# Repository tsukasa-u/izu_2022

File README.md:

# izu_2022
 
.sch & .brd can be opened with Eagle

2022伊豆大島共同打上実験で打ち上げる要諦だった機体に搭載されていた基板です。打ち上げ用ではありますが、回路に不具合があるため動作は保証できません。

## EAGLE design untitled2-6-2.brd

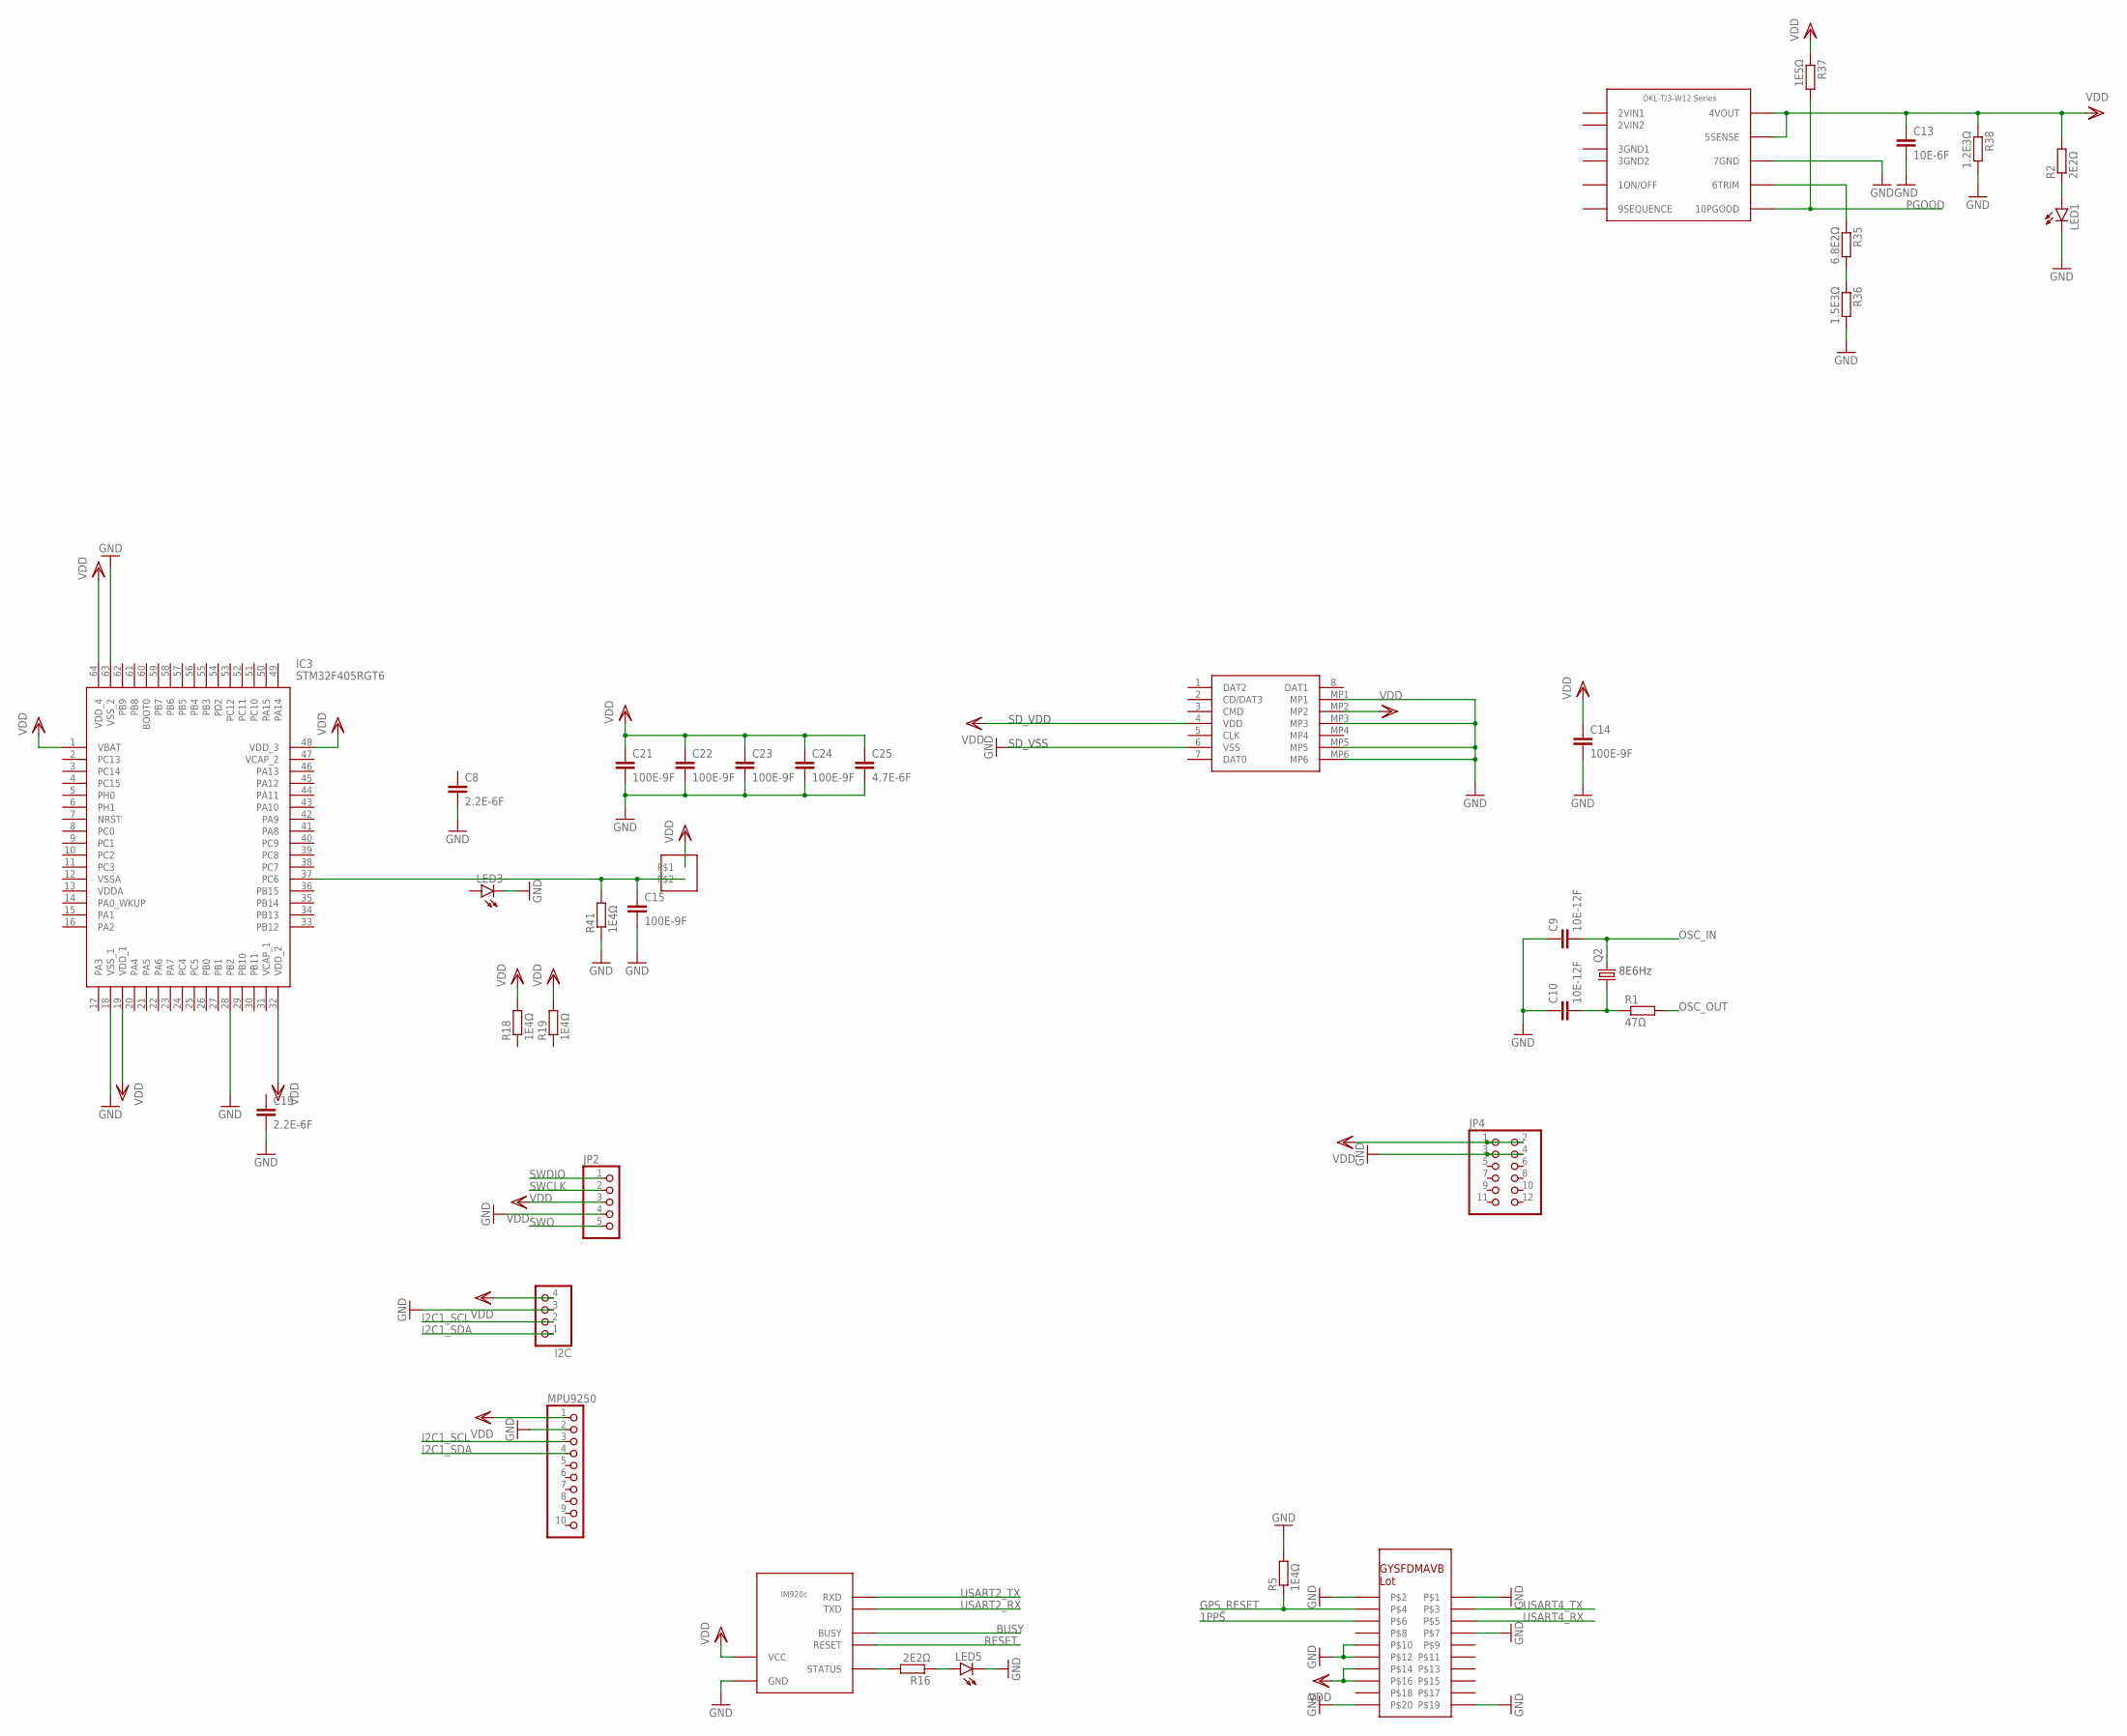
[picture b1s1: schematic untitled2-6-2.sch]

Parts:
C8, C19: 2.2E-6F; C0805
C9, C10: 10E-12F; C0805
C13: 10E-6F; C0805
C14, C15, C21, C22, C23, C24: 100E-9F; C0805
C25: 4.7E-6F; C0805
I2C: PINHD-1X4; 1X04
IC3: STM32F405RGT6; QFP50P1200X1200X160-64N
J1: DM3AT-SF-PEJM5; DM3ATSFPEJM5
JP2: PINHD-1X5; 1X05
JP4: PINHD-2X6; 2X06
LED1, LED3, LED5: LEDCHIP-LED0805; CHIP-LED0805
MPU9250: PINHD-1X10; 1X10
Q2: CRYSTALCTS406; CTS406
R1: 47Ω; R0603
R2, R16: 2E2Ω; R0603
R5, R18, R19, R41: 1E4Ω; R0603
R35: 6.8E2Ω; R0603
R36: 1.5E3Ω; R0603
R37: 1E5Ω; R0603
R38: 1.2E3Ω; R0603
U$3: OKL-T/3-W12SERIES
U$4: GYSFDMAXB_LOT
U$5: IM920C
U$10: B2B-XH-A

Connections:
1PPS: U$4.P$6
BUSY: U$5.BUSY
GND: C8.2, C9.1, C10.1, C13.2, C14.2, C15.2, C19.2, C21.2, C22.2, C23.2, C24.2, C25.2, I2C.3, IC3.18 (VSS_1), IC3.28 (PB2), IC3.63 (VSS_2), J1.6 (VSS), J1.MP1, J1.MP3, J1.MP5, J1.MP6, JP2.4, JP4.3, JP4.4, LED1.C, LED3.C, LED5.C, MPU9250.2, R5.2, R36.2, R38.2, R41.1, U$3.7GND, U$4.P$1, U$4.P$2, U$4.P$7, U$4.P$10, U$4.P$12, U$4.P$19, U$4.P$20, U$5.GND
GPS_RESET: R5.1, U$4.P$4
I2C1_SCL: I2C.2, MPU9250.3
I2C1_SDA: I2C.1, MPU9250.4
unnamed: R16.2, U$5.STATUS
unnamed: LED1.A, R2.1
unnamed: C15.1, IC3.37 (PC6), R41.2, U$10.P$2
unnamed: C10.2, Q2.1, R1.1
unnamed: R35.1, U$3.6TRIM
unnamed: R35.2, R36.1
unnamed: LED5.A, R16.1
OSC_IN: C9.2, Q2.3 (2)
OSC_OUT: R1.2
PGOOD: R37.2, U$3.10PGOOD
RESET: U$5.RESET
SWCLK: JP2.2
SWDIO: JP2.1
SWO: JP2.5
USART2_RX: U$5.TXD
USART2_TX: U$5.RXD
USART4_RX: U$4.P$5
USART4_TX: U$4.P$3
VDD: C13.1, C14.1, C21.1, C22.1, C23.1, C24.1, C25.1, I2C.4, IC3.1 (VBAT), IC3.19 (VDD_1), IC3.32 (VDD_2), IC3.48 (VDD_3), IC3.64 (VDD_4), J1.4 (VDD), J1.MP2, JP2.3, JP4.1, JP4.2, MPU9250.1, R2.2, R18.2, R19.2, R37.1, R38.1, U$3.4VOUT, U$3.5SENSE, U$4.P$14, U$4.P$16, U$5.VCC, U$10.P$1

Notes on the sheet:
8E6Hz
SD_VDD
SD_VSS

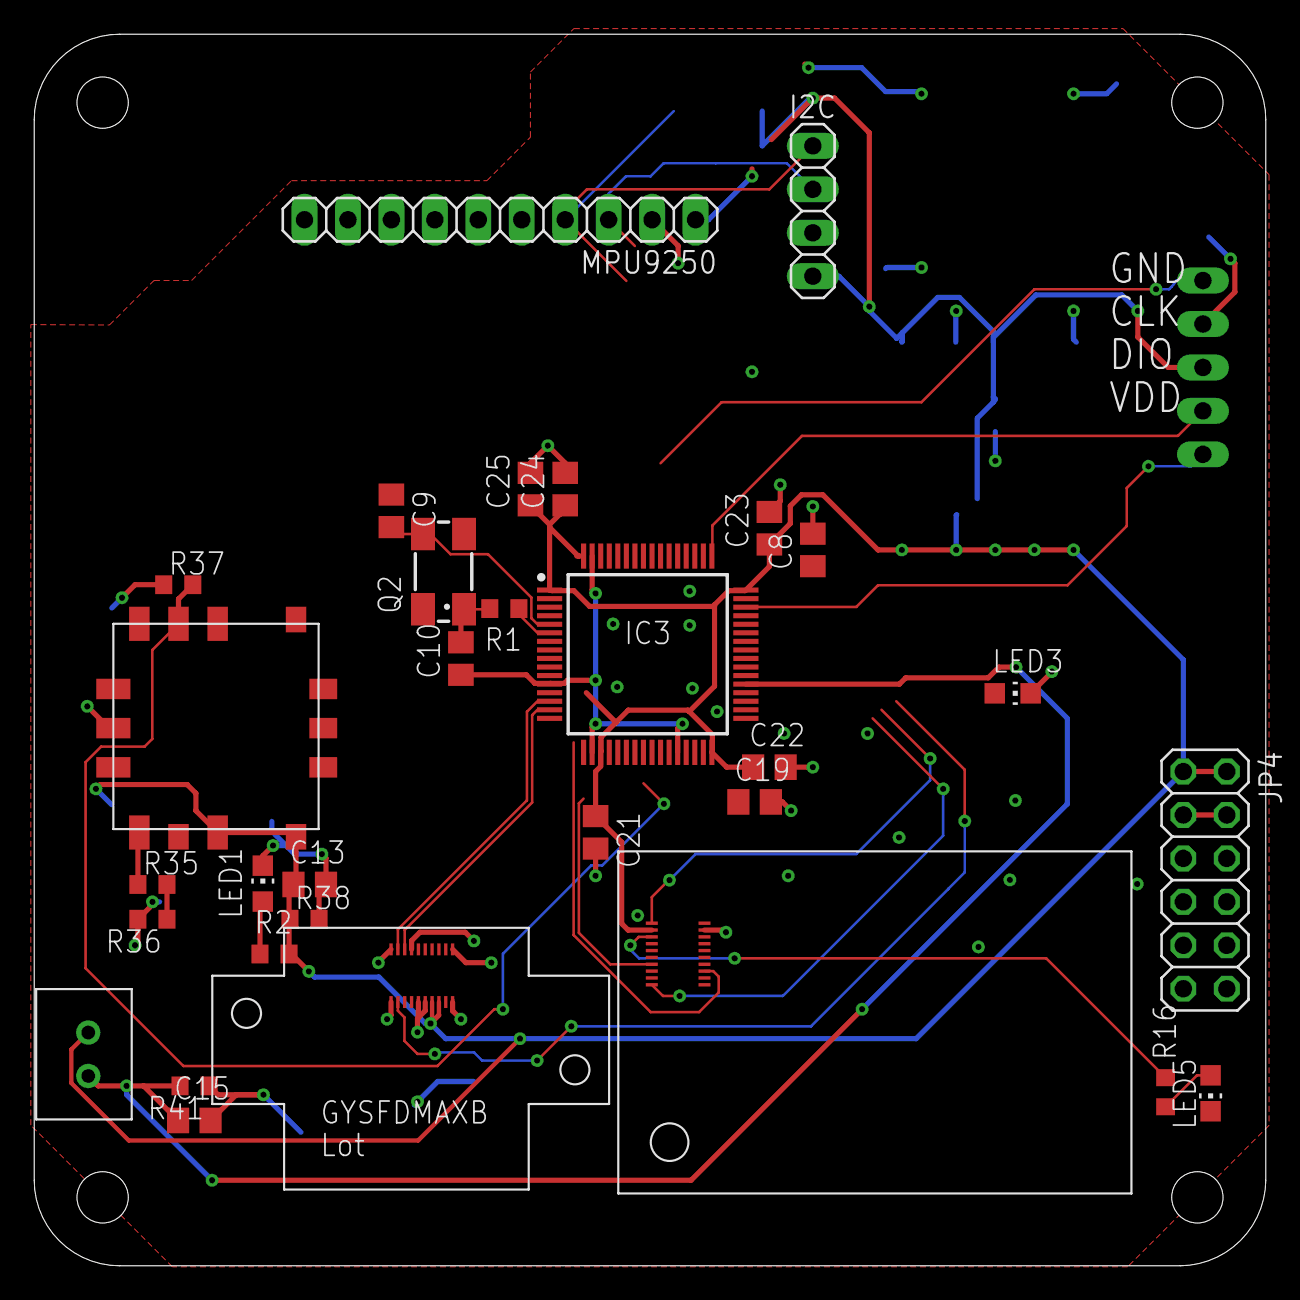
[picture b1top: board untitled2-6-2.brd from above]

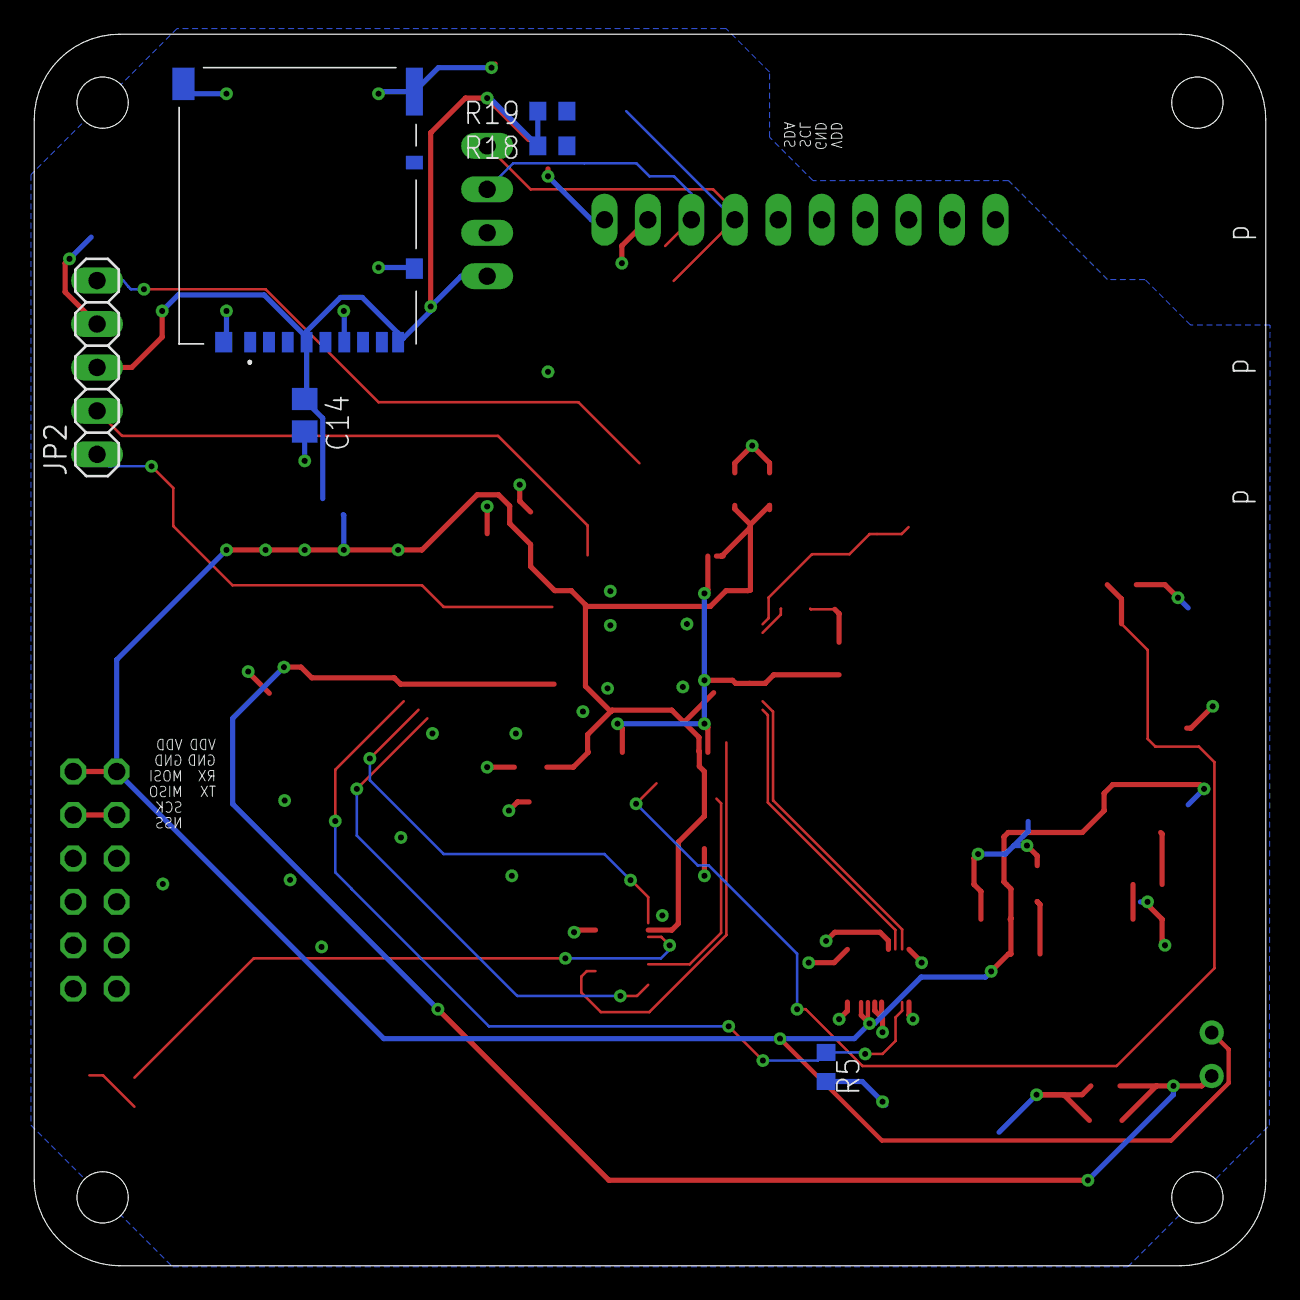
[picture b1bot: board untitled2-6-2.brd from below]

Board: 2 copper layers, 72.0 x 72.0 mm, 37 parts (6 on the bottom side), 14 nets.

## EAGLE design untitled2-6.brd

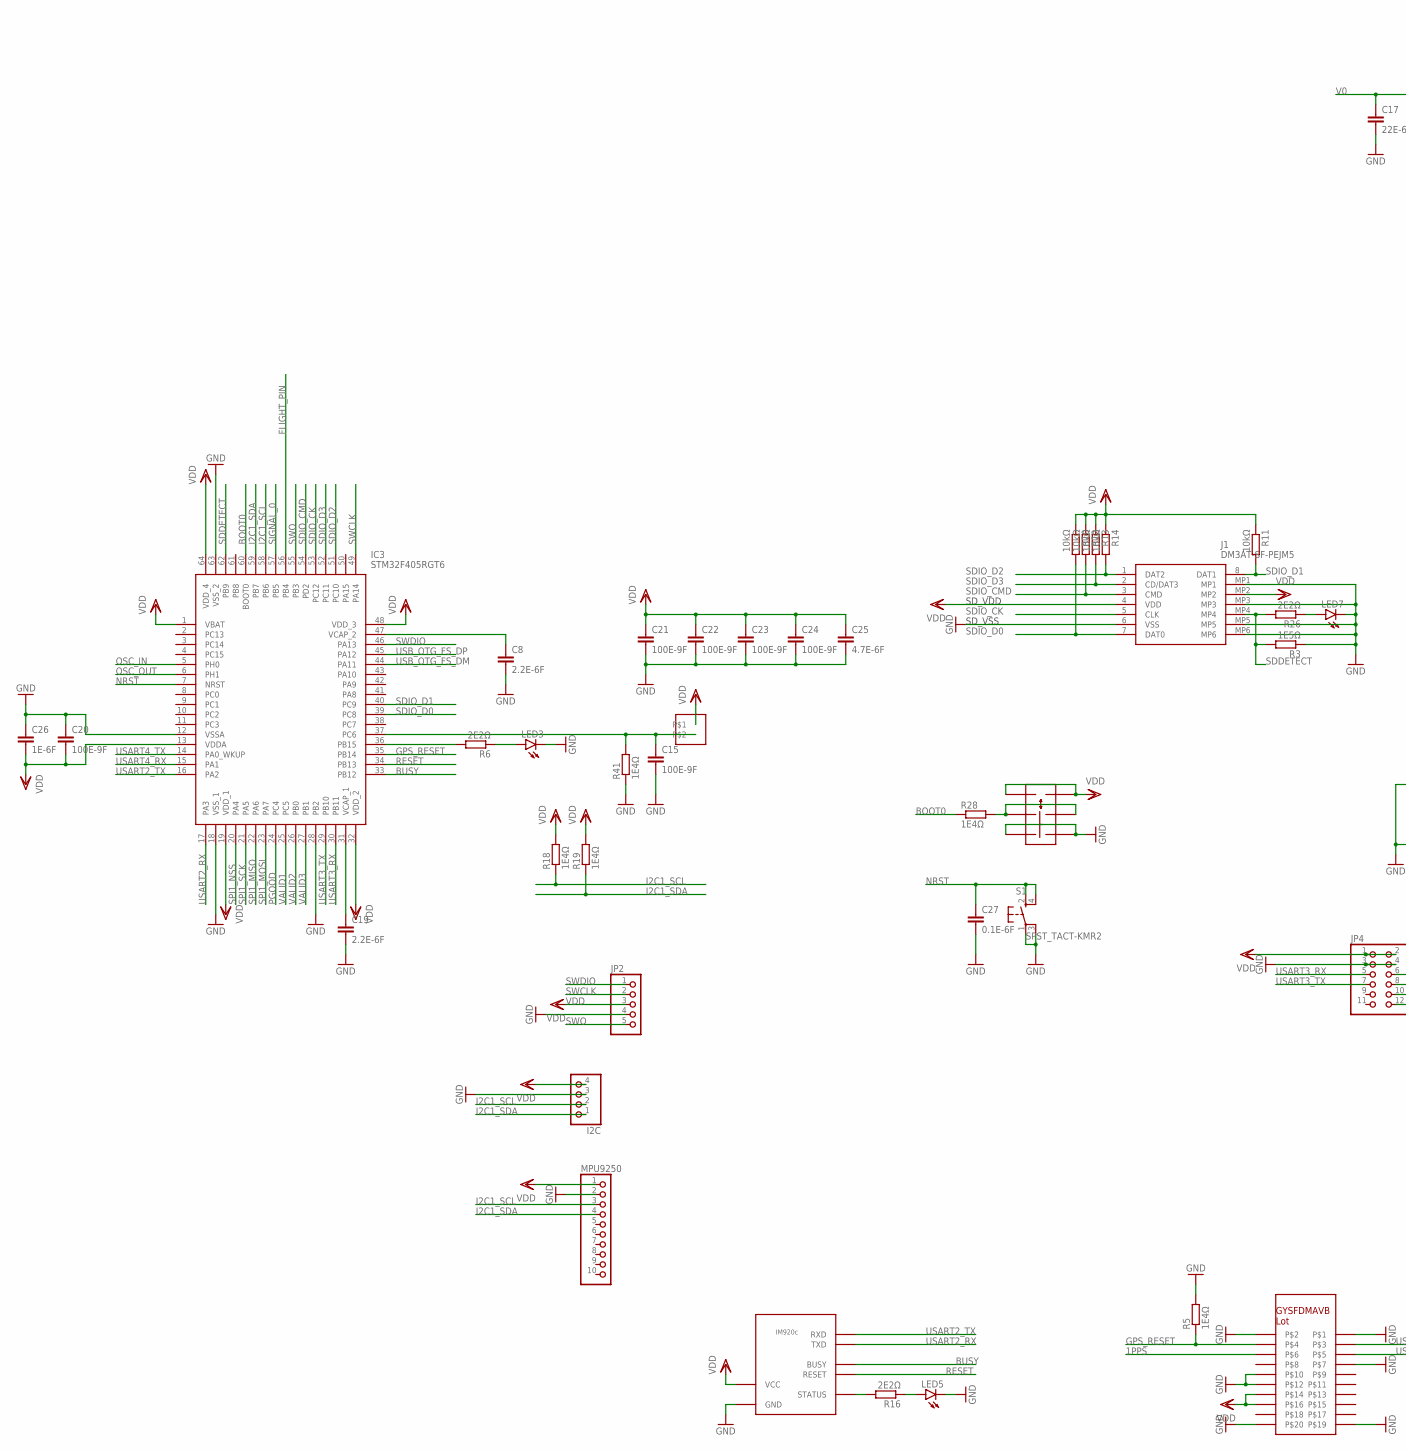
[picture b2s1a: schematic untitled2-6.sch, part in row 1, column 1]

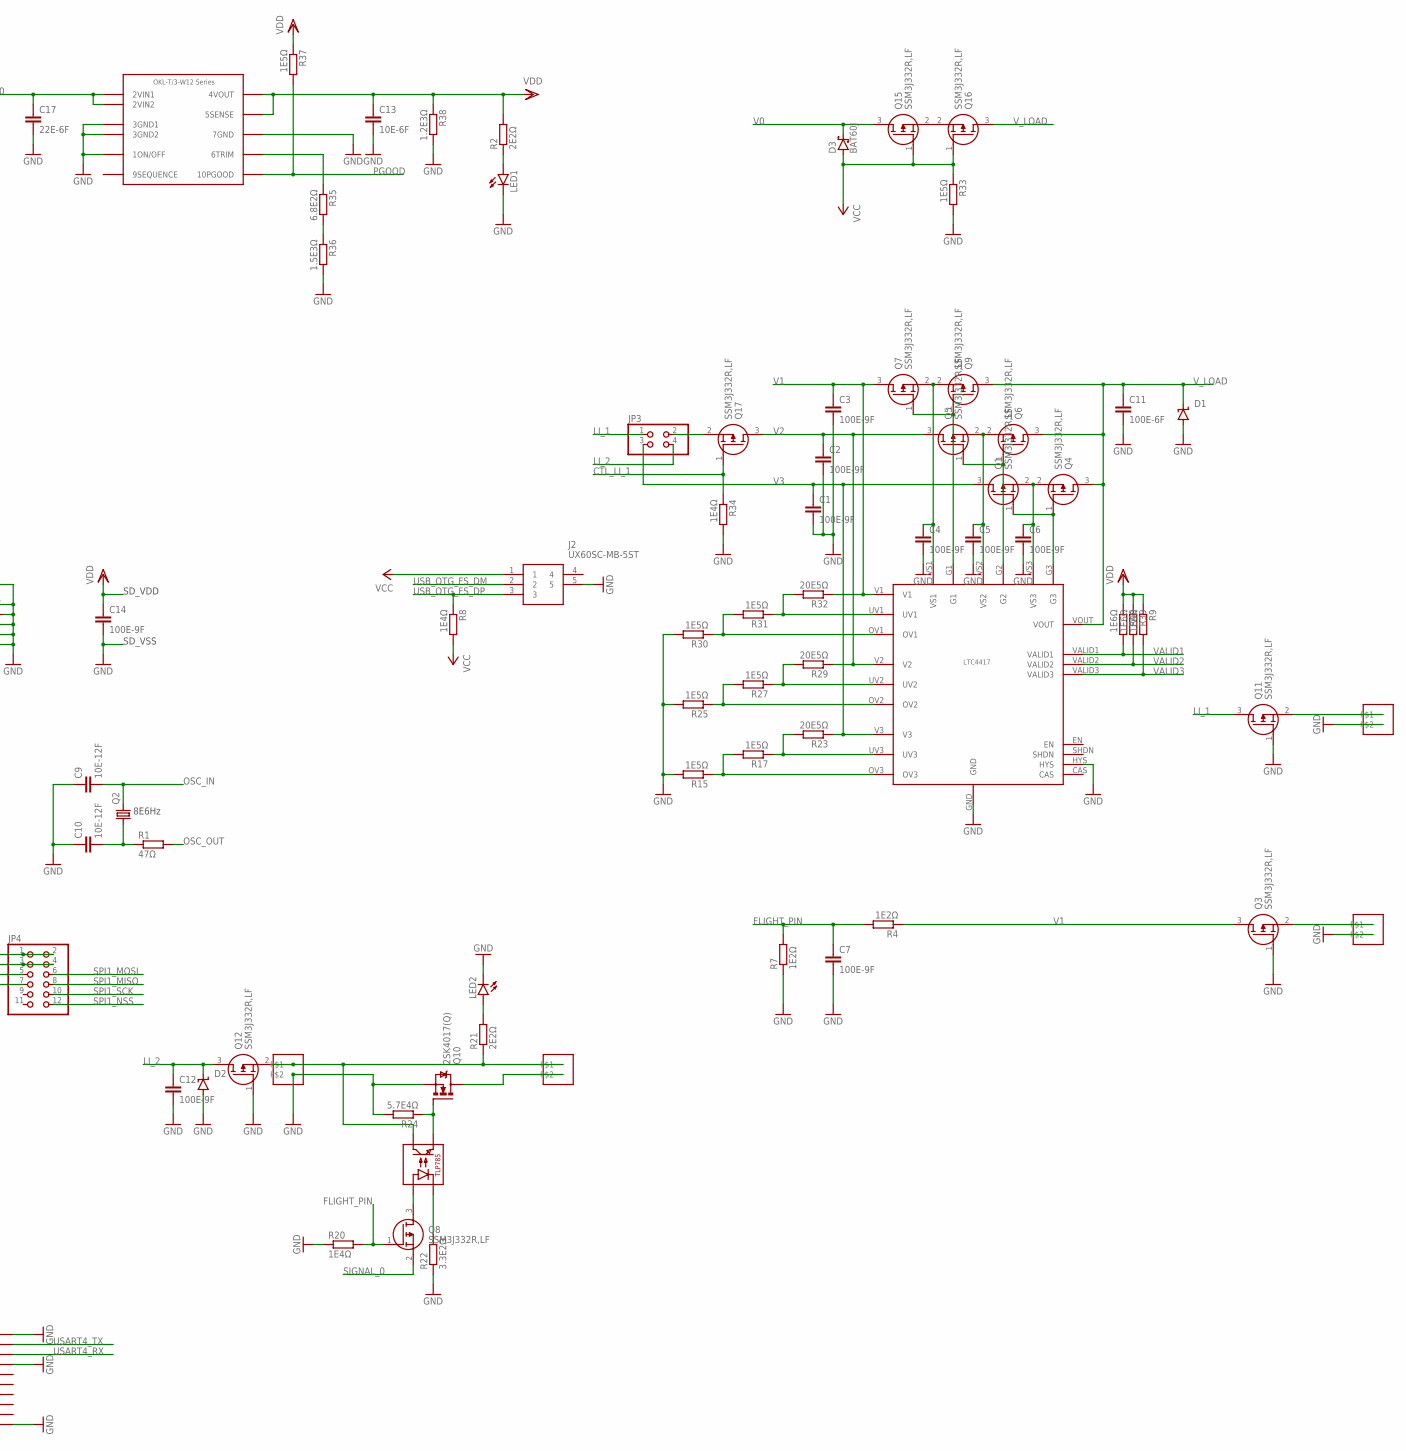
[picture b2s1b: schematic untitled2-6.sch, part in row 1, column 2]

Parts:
C1, C2, C3, C4, C5, C6, C7, C12, C14, C15, C20, C21, C22, C23, C24: 100E-9F; C0805
C8, C19: 2.2E-6F; C0805
C9, C10: 10E-12F; C0805
C11: 100E-6F; C0805
C13: 10E-6F; C0805
C17: 22E-6F; C0805
C25: 4.7E-6F; C0805
C26: 1E-6F; C0805
C27: 0.1E-6F; C0805
D1, D2: SUPPRESSOR-SMBJ; SMBJ
D3: BAT60J; SOD323_ST
I2C: PINHD-1X4; 1X04
IC3: STM32F405RGT6; QFP50P1200X1200X160-64N
J1: DM3AT-SF-PEJM5; DM3ATSFPEJM5
J2: UX60SC-MB-5ST
JP2: PINHD-1X5; 1X05
JP3: PINHD-2X2; 2X02
JP4: PINHD-2X6; 2X06
LED1, LED2, LED3, LED5, LED7: LEDCHIP-LED0805; CHIP-LED0805
MPU9250: PINHD-1X10; 1X10
Q1, Q3, Q4, Q5, Q6, Q7, Q8, Q9, Q11, Q12, Q15, Q16, Q17: SSM3J332R,LF; 2-3Z1S(SOT-23F)
Q2: CRYSTALCTS406; CTS406
Q10: 2SK4017(Q); TO230P230X650X740-3P
R1: 47Ω; R0603
R2, R6, R16, R21, R26: 2E2Ω; R0603
R3, R15, R17, R25, R27, R30, R31, R33, R37: 1E5Ω; R0603
R4, R7: 1E2Ω; R0603
R5, R8, R18, R19, R20, R28, R34, R41: 1E4Ω; R0603
R9, R39, R40: 1E6Ω; R0603
R10, R11, R12, R13, R14: 10kΩ; R0603
R22: 3.3E2Ω; R0603
R23, R29, R32: 20E5Ω; R0603
R24: 5.7E4Ω; R0603
R35: 6.8E2Ω; R0603
R36: 1.5E3Ω; R0603
R38: 1.2E3Ω; R0603
S1: SPST_TACT-KMR2; KMR2
TRANSISTER2: TLP785
U$1, U$6, U$7, U$8, U$10: B2B-XH-A
U$2: LTC4417
U$3: OKL-T/3-W12SERIES
U$4: GYSFDMAXB_LOT
U$5: IM920C
U$9: SSSS213202

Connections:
1PPS: U$4.P$6
BOOT0: IC3.60 (BOOT0), R28.1
BUSY: IC3.33 (PB12), U$5.BUSY
CTL_LI_1: Q17.1 (G), R34.1
FLIGHT_PIN: C7.1, IC3.56 (PB4), Q8.1 (G), R4.2, R7.2, R20.2
GND: C1.2, C2.2, C3.2, C4.2, C5.2, C6.2, C7.2, C8.2, C9.1, C10.1, C11.2, C12.2, C13.2, C14.2, C15.2, C17.2, C19.2, C20.1, C21.2, C22.2, C23.2, C24.2, C25.2, C26.1, C27.2, D1.A, D2.A, I2C.3, IC3.12 (VSSA), IC3.18 (VSS_1), IC3.28 (PB2), IC3.63 (VSS_2), J1.6 (VSS), J1.MP1, J1.MP3, J1.MP5, J1.MP6, J2.5, JP2.4, JP4.3, JP4.4, LED1.C, LED2.C, LED3.C, LED5.C, LED7.C, MPU9250.2, Q3.1 (G), Q10.3 (S), Q11.1 (G), Q12.1 (G), R3.1, R5.2, R7.1, R15.2, R20.1, R22.1, R24.2, R25.2, R30.2, R33.2, R34.2, R36.2, R38.2, R41.1, S1.1, S1.3 (P1), U$1.P$2, U$2.GND, U$2.HYS, U$3.1ON/OFF, U$3.3GND1, U$3.3TGND2 (3GND2), U$3.7GND, U$4.P$1, U$4.P$2, U$4.P$7, U$4.P$10, U$4.P$12, U$4.P$19, U$4.P$20, U$5.GND, U$6.P$2, U$8.P$2, U$9.P$5, U$9.P$6
GPS_RESET: IC3.35 (PB14), R5.1, U$4.P$4
I2C1_SCL: I2C.2, IC3.58 (PB6), MPU9250.3, R18.1
I2C1_SDA: I2C.1, IC3.59 (PB7), MPU9250.4, R19.1
LI_1: JP3.1, Q11.3 (D)
LI_2: C12.1, D2.C, JP3.4, Q12.3 (D)
unnamed: R16.2, U$5.STATUS
unnamed: LED1.A, R2.1
unnamed: IC3.36 (PB15), R6.2
unnamed: Q11.2 (S), U$1.P$1
unnamed: C15.1, IC3.37 (PC6), R41.2, U$10.P$2
unnamed: R15.1, R17.2, U$2.OV3
unnamed: C10.2, Q2.1, R1.1
unnamed: LED3.A, R6.1
unnamed: R17.1, R23.2, U$2.UV3
unnamed: Q1.1 (G), Q4.1 (G), U$2.G3
unnamed: R30.1, R31.2, U$2.OV1
unnamed: R31.1, R32.2, U$2.UV1
unnamed: R28.2, U$9.P$3, U$9.P$4
unnamed: Q10.2 (D), U$7.P$2
unnamed: R27.1, R29.2, U$2.UV2
unnamed: R25.1, R27.2, U$2.OV2
unnamed: C6.1, Q1.2 (S), Q4.2 (S), U$2.VS3
unnamed: Q3.2 (S), U$6.P$1
unnamed: Q12.2 (S), R21.1, TRANSISTER2.P$3, U$7.P$1, U$8.P$1
unnamed: C5.1, Q5.2 (S), Q6.2 (S), U$2.VS2
unnamed: Q5.1 (G), Q6.1 (G), U$2.G2
unnamed: C4.1, Q7.2 (S), Q9.2 (S), U$2.VS1
unnamed: Q7.1 (G), Q9.1 (G), U$2.G1
unnamed: R35.1, U$3.6TRIM
unnamed: Q15.2 (S), Q16.2 (S)
unnamed: R35.2, R36.1
unnamed: Q8.3 (D), TRANSISTER2.P$1
unnamed: Q10.1 (G), R24.1, TRANSISTER2.P$4
unnamed: LED5.A, R16.1
unnamed: JP3.2, Q17.2 (S)
unnamed: LED2.A, R21.2
unnamed: R22.2, TRANSISTER2.P$2
unnamed: LED7.A, R26.1
unnamed: C19.1, IC3.31 (VCAP_1)
unnamed: C8.1, IC3.47 (VCAP_2)
NRST: C27.1, IC3.7 (NRST), S1.2 (S), S1.4 (S1)
OSC_IN: C9.2, IC3.5 (PH0), Q2.3 (2)
OSC_OUT: IC3.6 (PH1), R1.2
PGOOD: IC3.24 (PC4), R37.2, U$3.10PGOOD
RESET: IC3.34 (PB13), U$5.RESET
SDDETECT: IC3.62 (PB9), J1.MP4, R3.2, R26.2
SDIO_CK: IC3.53 (PC12), J1.5 (CLK)
SDIO_CMD: IC3.54 (PD2), J1.3 (CMD), R12.2
SDIO_D0: IC3.39 (PC8), J1.7 (DAT0), R10.2
SDIO_D1: IC3.40 (PC9), J1.8 (DAT1), R11.2
SDIO_D2: IC3.51 (PC10), J1.1 (DAT2), R14.2
SDIO_D3: IC3.52 (PC11), J1.2 (CD/DAT3), R13.2
SIGNAL_0: IC3.57 (PB5), Q8.2 (S)
SPI1_MISO: IC3.22 (PA6), JP4.8
SPI1_MOSI: IC3.23 (PA7), JP4.6
SPI1_NSS: IC3.20 (PA4), JP4.12
SPI1_SCK: IC3.21 (PA5), JP4.10
SWCLK: IC3.49 (PA14), JP2.2
SWDIO: IC3.46 (PA13), JP2.1
SWO: IC3.55 (PB3), JP2.5
USART2_RX: IC3.17 (PA3), U$5.TXD
USART2_TX: IC3.16 (PA2), U$5.RXD
USART3_RX: IC3.30 (PB11), JP4.5
USART3_TX: IC3.29 (PB10), JP4.7
USART4_RX: IC3.15 (PA1), U$4.P$5
USART4_TX: IC3.14 (PA0_WKUP), U$4.P$3
USB_OTG_FS_DM: IC3.44 (PA11), J2.2
USB_OTG_FS_DP: IC3.45 (PA12), J2.3, R8.1
V0: C17.1, D3.C, Q15.3 (D), U$3.2VIN1, U$3.2VIN2
V1: C3.1, Q3.3 (D), Q7.3 (D), R4.1, R32.1, U$2.V1
V2: C2.1, Q5.3 (D), Q17.3 (D), R29.1, U$2.V2
V3: C1.1, JP3.3, Q1.3 (D), R23.1, U$2.V3
VALID1: IC3.25 (PC5), R40.2, U$2.VALID1
VALID2: IC3.26 (PB0), R39.2, U$2.VALID2
VALID3: IC3.27 (PB1), R9.2, U$2.VALID3
VCC: D3.A, J2.1, Q15.1 (G), Q16.1 (G), R8.2, R33.1
VDD: C13.1, C14.1, C20.2, C21.1, C22.1, C23.1, C24.1, C25.1, C26.2, I2C.4, IC3.1 (VBAT), IC3.13 (VDDA), IC3.19 (VDD_1), IC3.32 (VDD_2), IC3.48 (VDD_3), IC3.64 (VDD_4), J1.4 (VDD), J1.MP2, JP2.3, JP4.1, JP4.2, MPU9250.1, R2.2, R9.1, R10.1, R11.1, R12.1, R13.1, R14.1, R18.2, R19.2, R37.1, R38.1, R39.1, R40.1, U$3.4VOUT, U$3.5SENSE, U$4.P$14, U$4.P$16, U$5.VCC, U$9.P$1, U$9.P$2, U$10.P$1
V_LOAD: C11.1, D1.C, Q4.3 (D), Q6.3 (D), Q9.3 (D), Q16.3 (D), U$2.VOUT

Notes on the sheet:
8E6Hz
SD_VDD
SD_VSS

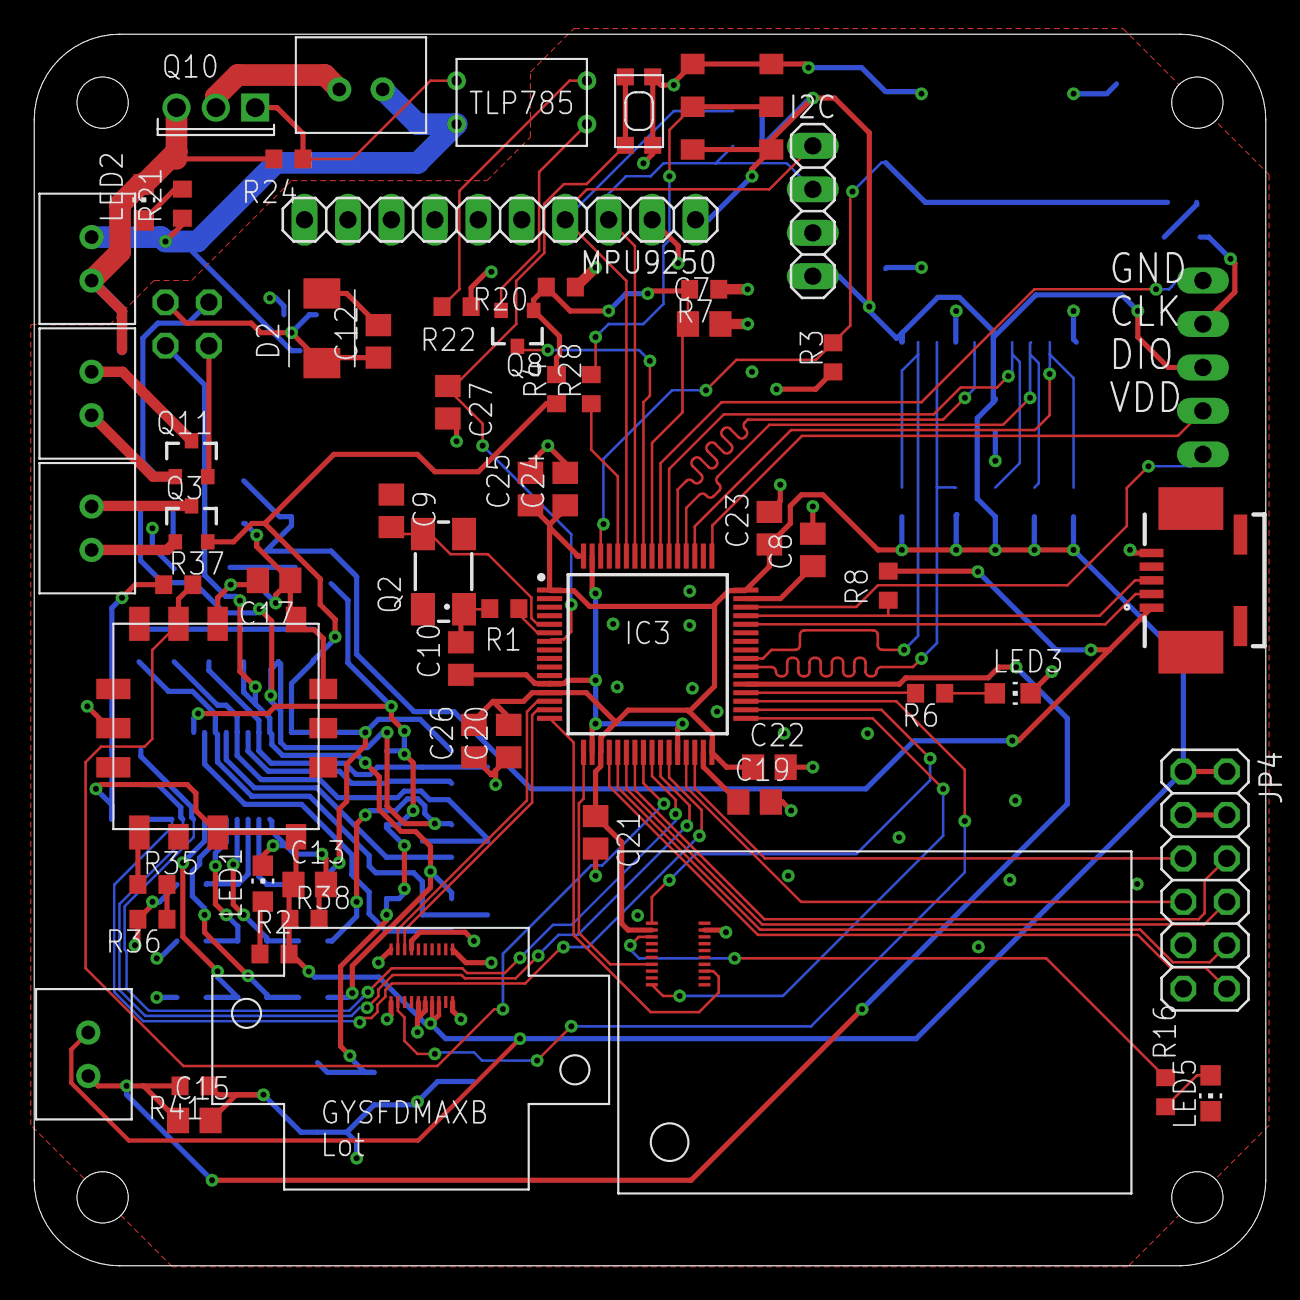
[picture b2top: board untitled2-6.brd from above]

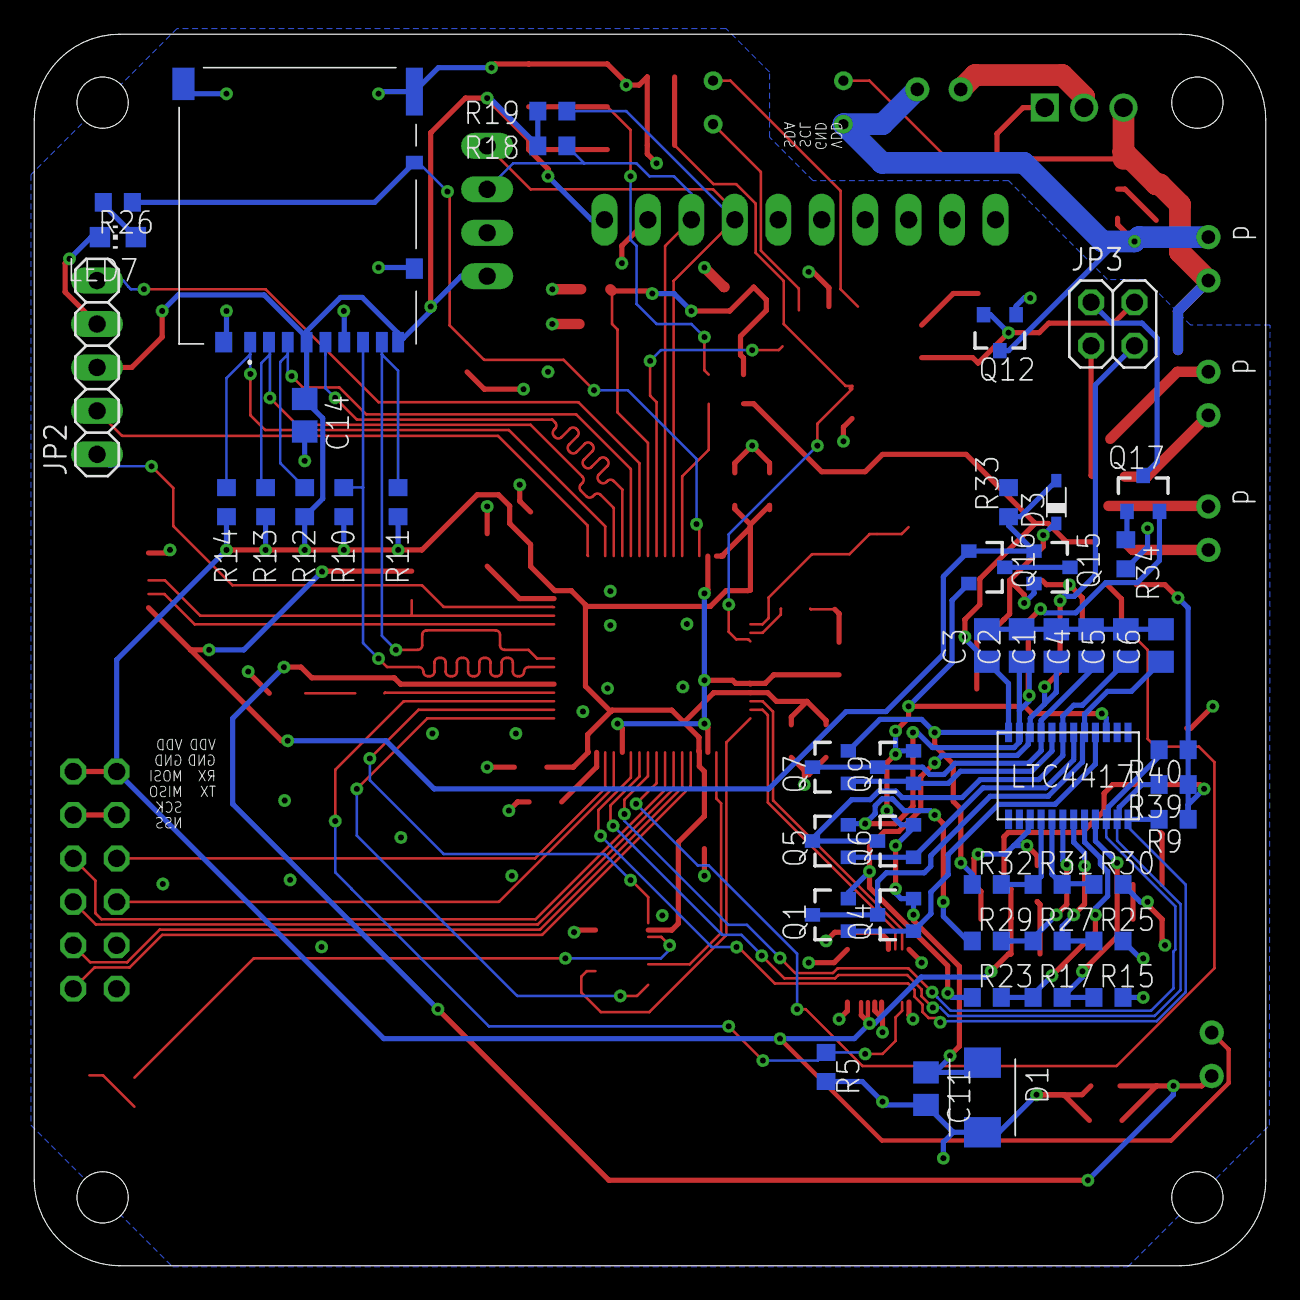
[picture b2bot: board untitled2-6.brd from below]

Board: 2 copper layers, 72.0 x 72.0 mm, 109 parts (48 on the bottom side), 83 nets.

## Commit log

2022-11-14 delete
